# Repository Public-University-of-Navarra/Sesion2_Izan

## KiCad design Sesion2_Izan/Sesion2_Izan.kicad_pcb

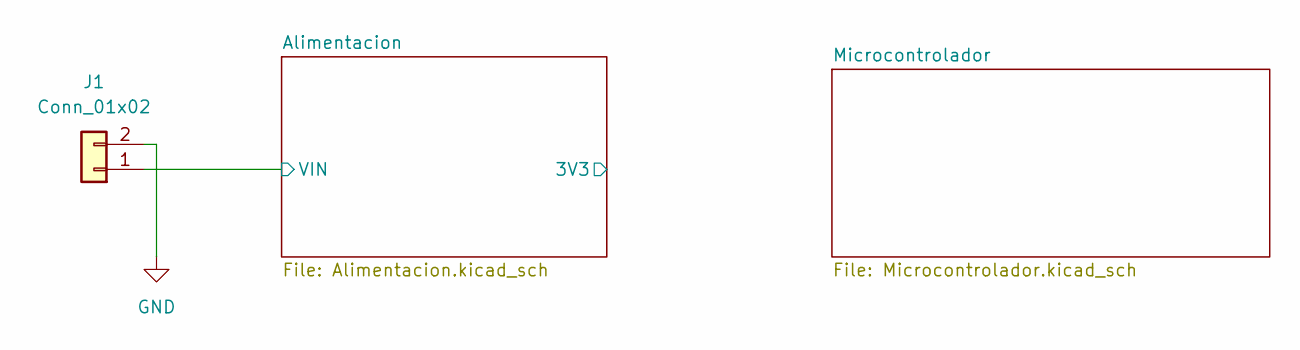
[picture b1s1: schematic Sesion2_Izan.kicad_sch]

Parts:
J1: Conn_01x02; TerminalBlock_Phoenix_PT-1,5-2-5.0-H_1x02_P5.00mm_Horizontal; MPN 1935161

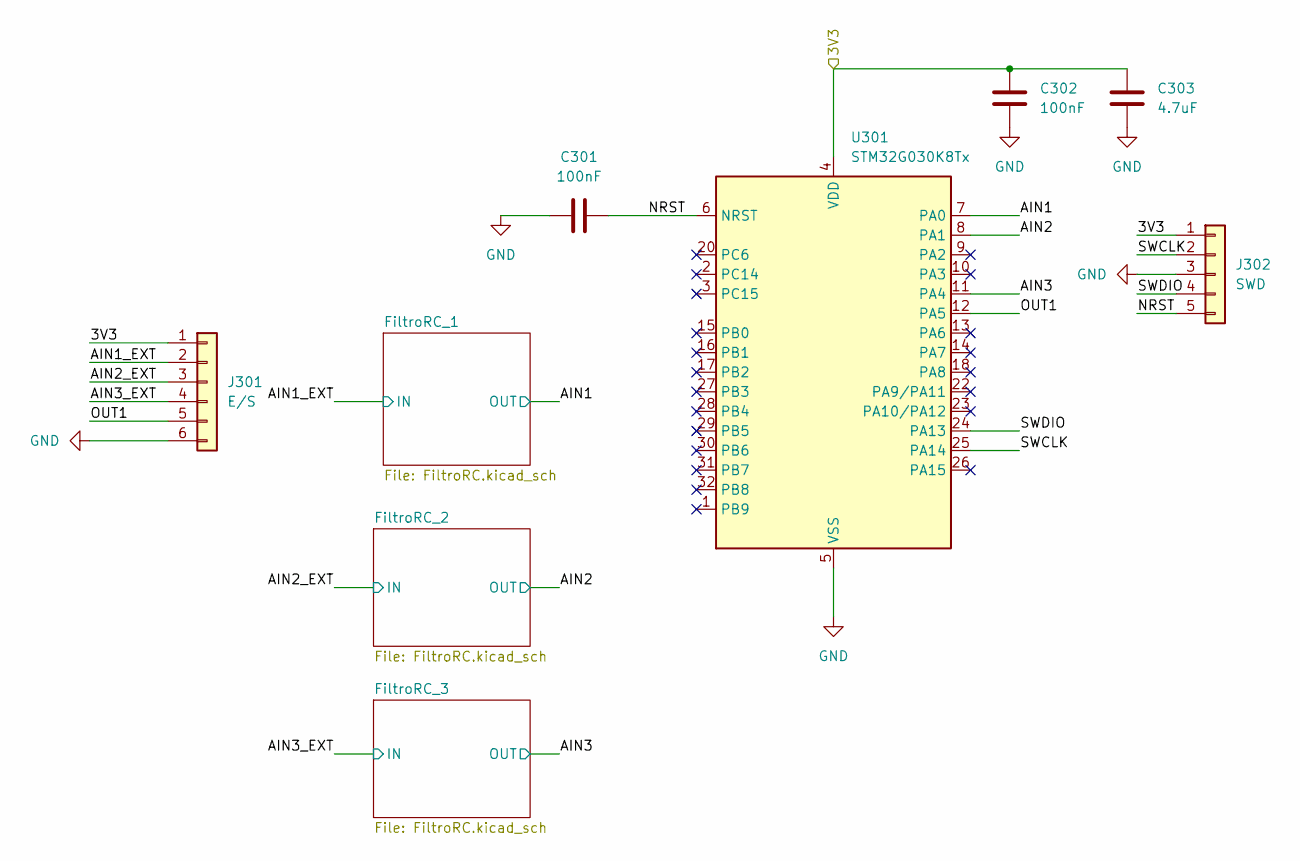
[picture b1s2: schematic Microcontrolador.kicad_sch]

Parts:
C301, C302: 100nF; C_0805_2012Metric_Pad1.18x1.45mm_HandSolder; MPN CL21B104KBCNFNC
C303: 4.7uF; C_0805_2012Metric_Pad1.18x1.45mm_HandSolder; MPN CL21B475KAFNNNE
J301: E/S; PinHeader_1x06_P2.54mm_Vertical; MPN TSW-106-07-G-S
J302: SWD; PinHeader_1x05_P2.54mm_Vertical; MPN TSW-105-07-G-S
U301: STM32G030K8Tx; LQFP-32_7x7mm_P0.8mm; MPN STM32G030K8T6

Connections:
/Microcontrolador/3V3: C302.1, C303.1, J301.1, J302.1, U301.4 (VDD); also elsewhere on the board
/Microcontrolador/AIN1: U301.7 (PA0); also elsewhere on the board
/Microcontrolador/AIN1_EXT: J301.2; also elsewhere on the board
/Microcontrolador/AIN2: U301.8 (PA1); also elsewhere on the board
/Microcontrolador/AIN2_EXT: J301.3; also elsewhere on the board
/Microcontrolador/AIN3: U301.11 (PA4); also elsewhere on the board
/Microcontrolador/AIN3_EXT: J301.4; also elsewhere on the board
/Microcontrolador/NRST: C301.1, J302.5, U301.6 (NRST)
/Microcontrolador/OUT1: J301.5, U301.12 (PA5)
/Microcontrolador/SWCLK: J302.2, U301.25 (PA14)
/Microcontrolador/SWDIO: J302.4, U301.24 (PA13)
GND: C301.2, C302.2, C303.2, J301.6, J302.3, U301.5 (VSS); also elsewhere on the board

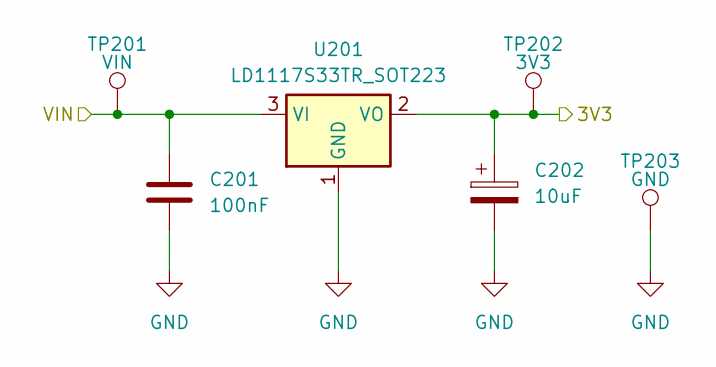
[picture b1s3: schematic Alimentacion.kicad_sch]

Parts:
C201: 100nF; C_0805_2012Metric_Pad1.18x1.45mm_HandSolder; MPN CL21B104KBCNFNC
C202: 10uF; CP_EIA-3216-18_Kemet-A; MPN T495A106K010ATE1K8
TP201: VIN; TestPoint_Keystone_5000-5004_Miniature; MPN 5003
TP202: 3V3; TestPoint_Keystone_5000-5004_Miniature; MPN 5000
TP203: GND; TestPoint_Keystone_5000-5004_Miniature; MPN 5001
U201: LD1117S33TR_SOT223; SOT-223-3_TabPin2; MPN LD1117S33TR

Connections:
/Alimentacion/VIN: C201.1, TP201.1 (1_1), U201.3 (VI); also elsewhere on the board
/Microcontrolador/3V3: C202.1, TP202.1 (1_1), U201.2 (VO); also elsewhere on the board
GND: C201.2, C202.2, TP203.1 (1_1), U201.1 (GND); also elsewhere on the board

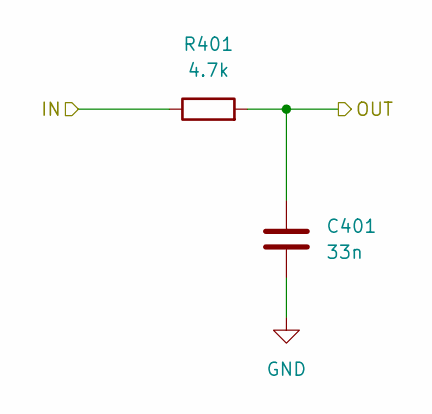
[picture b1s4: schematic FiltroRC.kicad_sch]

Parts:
C401: 33n; C_0805_2012Metric_Pad1.18x1.45mm_HandSolder; MPN C0805C333K5RACTU
R401: 4.7k; R_0805_2012Metric_Pad1.20x1.40mm_HandSolder; MPN ERJ-6ENF4701V

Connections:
/Microcontrolador/AIN1: C401.1, R401.2; also elsewhere on the board
/Microcontrolador/AIN1_EXT: R401.1; also elsewhere on the board
GND: C401.2; also elsewhere on the board

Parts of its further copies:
C501, C601: 33n; C_0805_2012Metric_Pad1.18x1.45mm_HandSolder; MPN C0805C333K5RACTU
R501, R601: 4.7k; R_0805_2012Metric_Pad1.20x1.40mm_HandSolder; MPN ERJ-6ENF4701V

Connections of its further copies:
/Microcontrolador/AIN2: C501.1, R501.2; also elsewhere on the board
/Microcontrolador/AIN2_EXT: R501.1; also elsewhere on the board
/Microcontrolador/AIN3: C601.1, R601.2; also elsewhere on the board
/Microcontrolador/AIN3_EXT: R601.1; also elsewhere on the board
GND: C501.2, C601.2; also elsewhere on the board

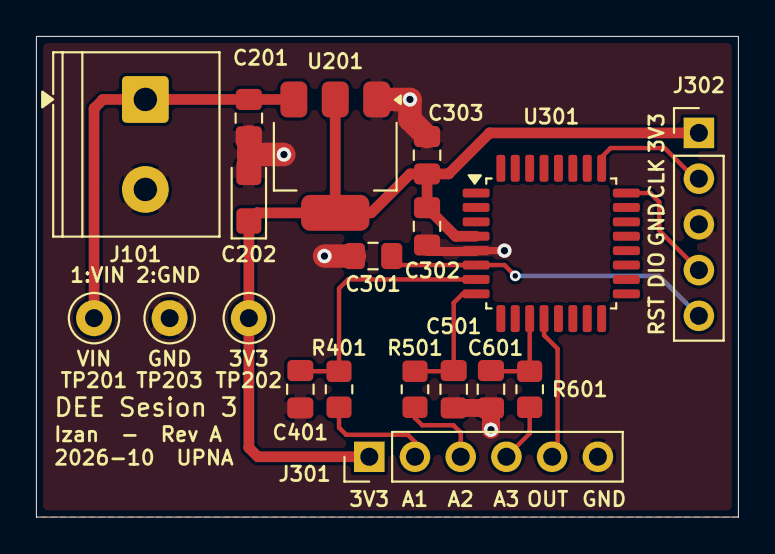
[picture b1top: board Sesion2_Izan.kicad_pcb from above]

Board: 2 copper layers, 39.0 x 26.7 mm, 19 parts (0 on the bottom side), 13 nets.

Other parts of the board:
J101: Conn_01x02; TerminalBlock_Phoenix_PT-1,5-2-5.0-H_1x02_P5.00mm_Horizontal

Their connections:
/Alimentacion/VIN: J101.1; also elsewhere on the board
GND: J101.2; also elsewhere on the board

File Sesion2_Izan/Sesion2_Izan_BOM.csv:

"Reference","Qty","Value","DNP","Exclude from BOM","Exclude from Board","Exclude from Simulation","Exclude from Position Files","Footprint","Datasheet","Manufacturer","MPN"
"C201,C301,C302","3","100nF","","","","","${EXCLUDE_FROM_POS_FILES}","Capacitor_SMD:C_0805_2012Metric_Pad1.18x1.45mm_HandSolder","","Samsung Electro-Mechanics","CL21B104KBCNFNC"
"C202","1","10uF","","","","","${EXCLUDE_FROM_POS_FILES}","Capacitor_Tantalum_SMD:CP_EIA-3216-18_Kemet-A","","KEMET","T495A106K010ATE1K8"
"C303","1","4.7uF","","","","","${EXCLUDE_FROM_POS_FILES}","Capacitor_SMD:C_0805_2012Metric_Pad1.18x1.45mm_HandSolder","","Samsung Electro-Mechanics","CL21B475KAFNNNE"
"C401,C501,C601","3","33n","","","","","${EXCLUDE_FROM_POS_FILES}","Capacitor_SMD:C_0805_2012Metric_Pad1.18x1.45mm_HandSolder","","KEMET","C0805C333K5RACTU"
"J101","1","Conn_01x02","","","","","${EXCLUDE_FROM_POS_FILES}","TerminalBlock_Phoenix:TerminalBlock_Phoenix_PT-1,5-2-5.0-H_1x02_P5.00mm_Horizontal","","Phoenix Contact","1935161"
"J301","1","E/S","","","","","${EXCLUDE_FROM_POS_FILES}","Connector_PinHeader_2.54mm:PinHeader_1x06_P2.54mm_Vertical","","Samtec","TSW-106-07-G-S"
"J302","1","SWD","","","","","${EXCLUDE_FROM_POS_FILES}","Connector_PinHeader_2.54mm:PinHeader_1x05_P2.54mm_Vertical","","Samtec","TSW-105-07-G-S"
"R401,R501,R601","3","4.7k","","","","","${EXCLUDE_FROM_POS_FILES}","Resistor_SMD:R_0805_2012Metric_Pad1.20x1.40mm_HandSolder","","Panasonic","ERJ-6ENF4701V"
"TP201","1","VIN","","","","","${EXCLUDE_FROM_POS_FILES}","TestPoint:TestPoint_Keystone_5000-5004_Miniature","","Keystone Electronics","5003"
"TP202","1","3V3","","","","","${EXCLUDE_FROM_POS_FILES}","TestPoint:TestPoint_Keystone_5000-5004_Miniature","","Keystone Electronics","5000"
"TP203","1","GND","","","","","${EXCLUDE_FROM_POS_FILES}","TestPoint:TestPoint_Keystone_5000-5004_Miniature","","Keystone Electronics","5001"
"U201","1","LD1117S33TR_SOT223","","","","","${EXCLUDE_FROM_POS_FILES}","Package_TO_SOT_SMD:SOT-223-3_TabPin2","http://www.st.com/st-web-ui/static/active/en/resource/techni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","STMicroelectronics","LD1117S33TR"
"U301","1","STM32G030K8Tx","","","","","${EXCLUDE_FROM_POS_FILES}","Package_QFP:LQFP-32_7x7mm_P0.8mm","https://www.st.com/resource/en/datasheet/stm32g030k8.pdf","STMicroelectronics","STM32G030K8T6"
